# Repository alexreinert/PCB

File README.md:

Dieses Werk ist lizenziert unter einer [Creative Commons Namensnennung - Nicht-kommerziell - Weitergabe unter gleichen Bedingungen 4.0 International Lizenz](http://creativecommons.org/licenses/by-nc-sa/4.0/).

Bei Nutzung der Platinen freue ich mich über Feedback und kleine Aufmerksamkeiten aus meiner [Amazon Wunschliste](https://www.amazon.de/gp/registry/wishlist/3NNUQIQO20AAP/ref=nav_wishlist_lists_1).

Viele Platinen gibt es auch im offiziellen Shop [viopcb](https://www.viopcb.de/).

# PCB
## HB-RF-ETH
Eine Platine um die Homematic Funkmodule HM-MOD-RPI-PCB und RPI-RF-MOD per Netzwerk anschließen zu können.

[Schaltplan](HB-RF-ETH/HB-RF-ETH.pdf)
Die Platine benötigt spezielle Treiber, welche in [debmatic](https://github.com/alexreinert/debmatic) und in [piVCCU3](https://github.com/alexreinert/piVCCU) verfügbar sind.
Eine passende Firmware findet sich unter [HB-RF-ETH](https://github.com/alexreinert/HB-RF-ETH).
Diese Platine ist auch als fertig bestückter Bausatz erhältlich bei [viopcb](https://www.viopcb.de/produkt/bausatz-hb-rf-eth-mit-poe/).

### Benötigte Bauteile:
Siehe Schaltplan

## HB-RF-USB-2
Eine Platine um die Homematic Funkmodule HM-MOD-RPI-PCB und RPI-RF-MOD per USB anschließen zu können.

[Schaltplan](HB-RF-USB-2/HB-RF-USB-2.pdf)
Die Platine benötigt spezielle Treiber, diese sind in [debmatic](https://github.com/alexreinert/debmatic) ab Version 3.51.6-45 und in [piVCCU3](https://github.com/alexreinert/piVCCU) ab Version 3.51.6-40 eingebaut.
Diese Platine ist auch als fertig bestückter Bausatz erhältlich bei [viopcb](https://www.viopcb.de/produkt/bausatz-hb-rf-usb-2/).

### Benötigte Bauteile:
* 1x CP2102N (U1)
* 1x SRV05-4 (U2)
* 2x Kerko 10nF 0402 (C1, C2)
* 6x Kerko 100nF 0402 (C3, C5, C7, C8, C9, C10)
* 2x Kerko 4.7uF 0603 (C4, C6)
* 1x Ferrite Bead 100Ohm, 800mA 0805 (L1)
* 2x AO3401A (Q1, Q2)
* 1x AO3400A (Q3)
* 1x S8050 (Q4)
* 1x Widerstand 1M 0402 (R1)
* 3x Widerstand 1K 0402 (R2, R6, R7)
* 4x Widerstand 10K 0402 (R3, R4, R5, R8)
* 1x USB B Buchse B1HSW6 (J1)
* 1x Pinheader 2x20 (J2)

### EEPROM flashen
[Anleitung](https://hb-programmer.areinert.de)

## HB-RF-USB
Eine Platine um die Homematic Funkmodule HM-MOD-RPI-PCB und RPI-RF-MOD per USB anschließen zu können.

[Schaltplan](HB-RF-USB/HB-RF-USB.pdf)
Die Platine benötigt spezielle Treiber, diese sind in [piVCCU3](https://github.com/alexreinert/piVCCU) ab Version 3.41.11-13, in [debmatic](https://github.com/alexreinert/debmatic) und in [RaspberryMatic](https://github.com/jens-maus/RaspberryMatic) ab Version 3.41.11.20190126 eingebaut.
Diese Platine ist auch erhältlich bei [viopcb](https://www.viopcb.de/produkt/platine-hb-rf-usb/)

### Benötigte Bauteile:
* 1x FTDI FT232RL (U1)
* 1x Micro USB Connector U-F-M5DD-Y-1 (bis Rev. 1.3 MK5P Micro USB Connector)
* 1x Kerko 4.7nF 0805 (C9)
* 1x Kerko 10nF 0805 (C7)
* 6x Kerko 100nF 0805 (C1-C6)
* 1x Kerko 4.7uF 0805 (C8)
* 2x Widerstand 1K 0805 (R2, R3)
* 2x Widerstand 10K 0805 (R1, R5)
* 1x Widerstand 1M 0805 (R4)
* 1x Ferritperle 30 Ohm 0805 (L1)
* 2x IRLML6402 (Q1, Q2)
* 1x IRLML2502 (Q3)
* 1x Pinheader 2*6
* 1x Pinheader 2*20

### EEPROM flashen
[Anleitung](https://hb-programmer.areinert.de)

## HB-UNI-SEN-BATT
Eine universelle Platine für Homebrew Geräte basierend auf [AskSin++ Library](https://github.com/pa-pa/AskSinPP)

[Schaltplan](HB-UNI-SEN-BATT/HB-UNI-SEN-BATT.pdf)
Diese Platine ist auch erhältlich bei [viopcb](https://www.viopcb.de/produkt/platine-hb-uni-sen-batt/).

### Benötigte Bauteile:
* Arduino Pro Mini 3.3V 8Mhz (The Simple)
* CC1101 Modulplatine 868MHz
* 2x LEDs 3mm Low Current (Pin 4 und 5)
* 2x 470Ohm Widerstände (Vorwiderstand für LEDs)
* Elko 10uF 1,5mm
* 2x Goobay Batteriehalter Mignon Print
* Mikroschalter 6*6mm
* Stiftleiste RM 2mm 1x8 Pin (Für CC1101)
* Stiftleiste RM 2,54MM (nach Bedarf)
* IRLU024N (optional für Verpolungsschutz)
* 100KOhm Widerstand (optional für Verpolungsschutz)
* 2x 10KOhm Widerstand (optional Pullup für I2C)

### Passendes Gehäuse
* Camdenboss CBRS01SWH und CBRS01VWH

### Hinweise
* Achtung: Kein Überspannungschutz vorhanden
* Der Verpolungsschutz ist optional. Dafür Bauteil Q1 (IRLU024N) und R3 (100KOhm Widerstand) bestücken. Alternativ J8 auf der Platinenrückseite brücken um ohne Verpolungsschutz zu arbeiten.

## HB-UNI-SEN-PCB
Eine universelle Platine für Homebrew Geräte basierend auf [AskSin++ Library](https://github.com/pa-pa/AskSinPP)

[Schaltplan](HB-UNI-SEN-PCB/HB-UNI-SEN-PCB.pdf)
Diese Platine ist auch erhältlich bei [viopcb](https://www.viopcb.de/produkt/platine-hb-uni-sen-pcb/).

### Benötigte Bauteile:
* Arduino Pro Mini 3.3V 8Mhz (The Simple)
* CC1101 Modulplatine 868MHz
* 1x LEDs 3mm Low Current (Pin 4)
* 1x 470Ohm Widerstände (Vorwiderstand für LEDs)
* Mikroschalter 6*6mm
* Stiftleiste RM 2mm 1x8 Pin (Für CC1101)
* Stiftleiste RM 2,54MM (nach Bedarf)
* Optional: 2x 10KOhm Widerstand und 2x 10KOhm PTC (Temperaturmessung mit PTC an A0 und A1)

### Hinweise
* Achtung: kein Verpolungs- oder Überspannungschutz vorhanden
* Am I2C sind keine Pullups vorhanden, da diese im Regelfall auf I2C Platinen bereits integriert sind
* Aktuell fehlt noch ein Kondensator am VCC vom CC1101.

## HB-UNI-644 (Rev. 2)
Eine universelle Platine für Homebrew Geräte basierend auf [AskSin++ Library](https://github.com/pa-pa/AskSinPP) und dem ATmega644PA

[Schaltplan](HB-UNI-644/HB-UNI-644.pdf)
Diese Platine ist auch erhältlich bei [viopcb](https://www.viopcb.de/produkt/platine-hb-uni-644-rev-2/).

### Benötigte Bauteile:
#### Grundfunktion
* ATmega644PA oder ATmega1284P (TQFP44) (U1)
* CC1101 Modulplatine 868MHz ggf. mit RM 2.0 Pinheader (U2)
* 1x Kerko 10uF 0805 (C13)
* 7x Kerko 100nF 0805 (C1-C6, C14)
* 2x Widerstand 330 Ohm 0805 (R2, R3)
* 1x Widerstand 10K Ohm 0805 (R1)
* 1x Triple Color LED Common Cathode THT (D1)
* 1x Tactile Switch 2 Pin 6x3.5 SMD (SW1)
* 1x Quarz 8 Mhz HC49 THT (Y1) (optional)
* 2x Kerko 22pF 0805 (C7, C8) (optional für Quarz)
* Pinheader nach Bedarf

#### Power Option 1: Batteriebetrieb mit Step-Up
* 2x Goobay Batteriehalter Mignon Print
* 1x Widerstand 470K Ohm 0805 (R5)
* 1x Widerstand 100K Ohm 0805 (R6)
* 1x MAX1724EZK33 (U3)
* 1x LQH43CN100K03L (L1)
* 1x Kerko 10uF 0805 (C9)
* 1x Kerko 33uF 1206 (C10)
##### Verpolungsschutz und Überlastschutz
* 1x IRLML6244 (Q1)
* 1x Widerstand 100K Ohm 0805 (R4)
* 1x PTC 6V/250mA 1206 (F1)

#### Power Option 2: Externe Stromversorgung mit 5-9V, 100mA
* 1x HT-7533-1 (U4)
* 1x Kerko 10uF 50V 1206 (C11)
* 1x Kerko 10uF 0805 (C12)
* 1x Elko 1000uF 8mm*12mm (C15)
##### Verpolungsschutz und Überlastschutz
* 1x IRLML5203 (Q2)
* 1x Widerstand 100K Ohm 0805 (R11)
* 1x PTC 16V/250mA 1206 (F1)

#### Power Option 3: Externe Stromversorgung 5-24V, 1A
* 1x [MP2315 Power Module](https://de.aliexpress.com/item/DC-DC-R-cktritt-Abw-rtswandler-Einstellbar-4-5-V-24-V-zu-5-V-3A/32833398745.html)
   Kontakt zum Trimmer durchtrennen, Lötbrücke bei 3.3V anbringen
* 1x Elko 1000uF 8mm*12mm (C15)
##### Verpolungsschutz und Überlastschutz
* 1x IRF4905S (Q3)
* 1x Widerstand 100K Ohm 0805 (R12)
* 1x Zener 16V MiniMelf (D2)
* 1x PTC 30V/2A 1206 (F1)

#### I2C Pullup Widerstände (optional)
* 2x Widerstand 10k Ohm 0805 (R7, R8)

#### Vorwiderstände für NTC Messung an A0 und A1
* 2x Widerstand 10k Ohm 0805 (R9, R10)

### Passendes Gehäuse
* Camdenboss CBRS01SWH und CBRS01VWH

### Betrieb mit 5V, 16MHz bei Netzbetrieb
* Der MC kann auch mit 5V und dann mit 16MHz betrieben werden, dafür müssen ggü. oben folgende Anpassungen gemacht werden:
* Nicht möglich bei Power Option 1
* Bei Power Option 2: HT-7550-1 statt HT-7533-1 uf U4, Eingangsspannung >= 6V
* Bei Power Option 3: Lötbrücke auf MP2315 Modul bei 5V statt bei 3.3V, Eingangsspannung >= 6V
* CC1101 auf Position U5 statt auf U2
* Nicht bestücken: C13, C14
* Quarz Y1 mit 16MHz statt 8MHz
* Zusätzliche Bauteile
   * 1x LM-3480-3.3 (U6)
   * 1x TXS0108EPWR (U7)
   * 3x Kerko 10uF 0805 (C16, C18, C19)
   * 3x Kerko 100nF 0805 (C17, C20, C21)
* ACHTUNG: Alle VCC Pins laufen dann auf 5V, auch z.B. die vom I2C

### Hinweise
* Auch wenn die meisten Bauteile SMD sind, so ist die Platine für Handlötung entwickelt. Dementsprechend sind alle Teile mind. 0805 mit vergrößerten Pads für Handlötung.
* Es darf immer nur eine Power Option genutzt und bestückt werden
* Die rechte Seite der Platine kann entfernt werden, wenn die Batteriehalter oder das MP2315 Power Module nicht benötigt werden, es laufen keine Leiterbahnen rechts der Fräsung (abgesehen von denen für die Batterie bzw. Power Module)
* Die Lötbrücke J2 muss immer geschlossen werden, außer es wird der Verpolungsschutz für Batteriebetrieb verwendet
* Falls eine externe Spannung von 3.3V ohne Spannungsanpassung, Verpolungsschutz und Überlastschutz verwendet werden soll, dann muss die Lötbrücke J4 geschlossen werden
* Die Anschlüsse an J9 sind zusammen mit J12 genau passend für die Platine CJMCU-2803 um an den Anschlüssen ein Darlington Array zu verwenden (Jeder der Ports ist dann mit 500mA belastbar)
* Beschriftung der Anschlüsse folgt dem Bobuino Pinout

## HB-UNI-SEN-WEA
Eine passende Platine für den [Wettersensor von Jérôme](https://github.com/jp112sdl/HB-UNI-Sen-WEA/)

[Schaltplan](HB-UNI-SEN-WEA/HB-UNI-SEN-WEA.pdf)
Diese Platine ist auch erhältlich bei [viopcb](https://www.viopcb.de/produkt/platine-hb-uni-sen-wea/).

### Benötigte Bauteile:
* Arduino Pro Mini 3.3V 8Mhz (The Simple)
* CC1101 Modulplatine 868MHz
* Elko 10uF 1,5mm
* Mikroschalter 6*6mm
* Kerko 1nf RM 2.5mm
* 10K Widerstand
* 100K Widerstand
* MPSA13 TO-92
* 4x Molex Spox 2-pol (Alternativ Stiftleiste oder Kabel direkt anlöten)
* 4x Molex Spox 4-pol (Alternativ Stiftleiste oder Kabel direkt anlöten)
* 1x Molex Spox 7-pol (Alternativ Stiftleiste oder Kabel direkt anlöten)
* Stiftleiste RM 2mm 1x8 Pin (Für CC1101)

### Hinweise
* Achtung: kein Verpolungs- oder Überspannungschutz vorhanden
* Am I2C sind keine Pullups vorhanden, da diese im Regelfall auf I2C Platinen bereits integriert sind

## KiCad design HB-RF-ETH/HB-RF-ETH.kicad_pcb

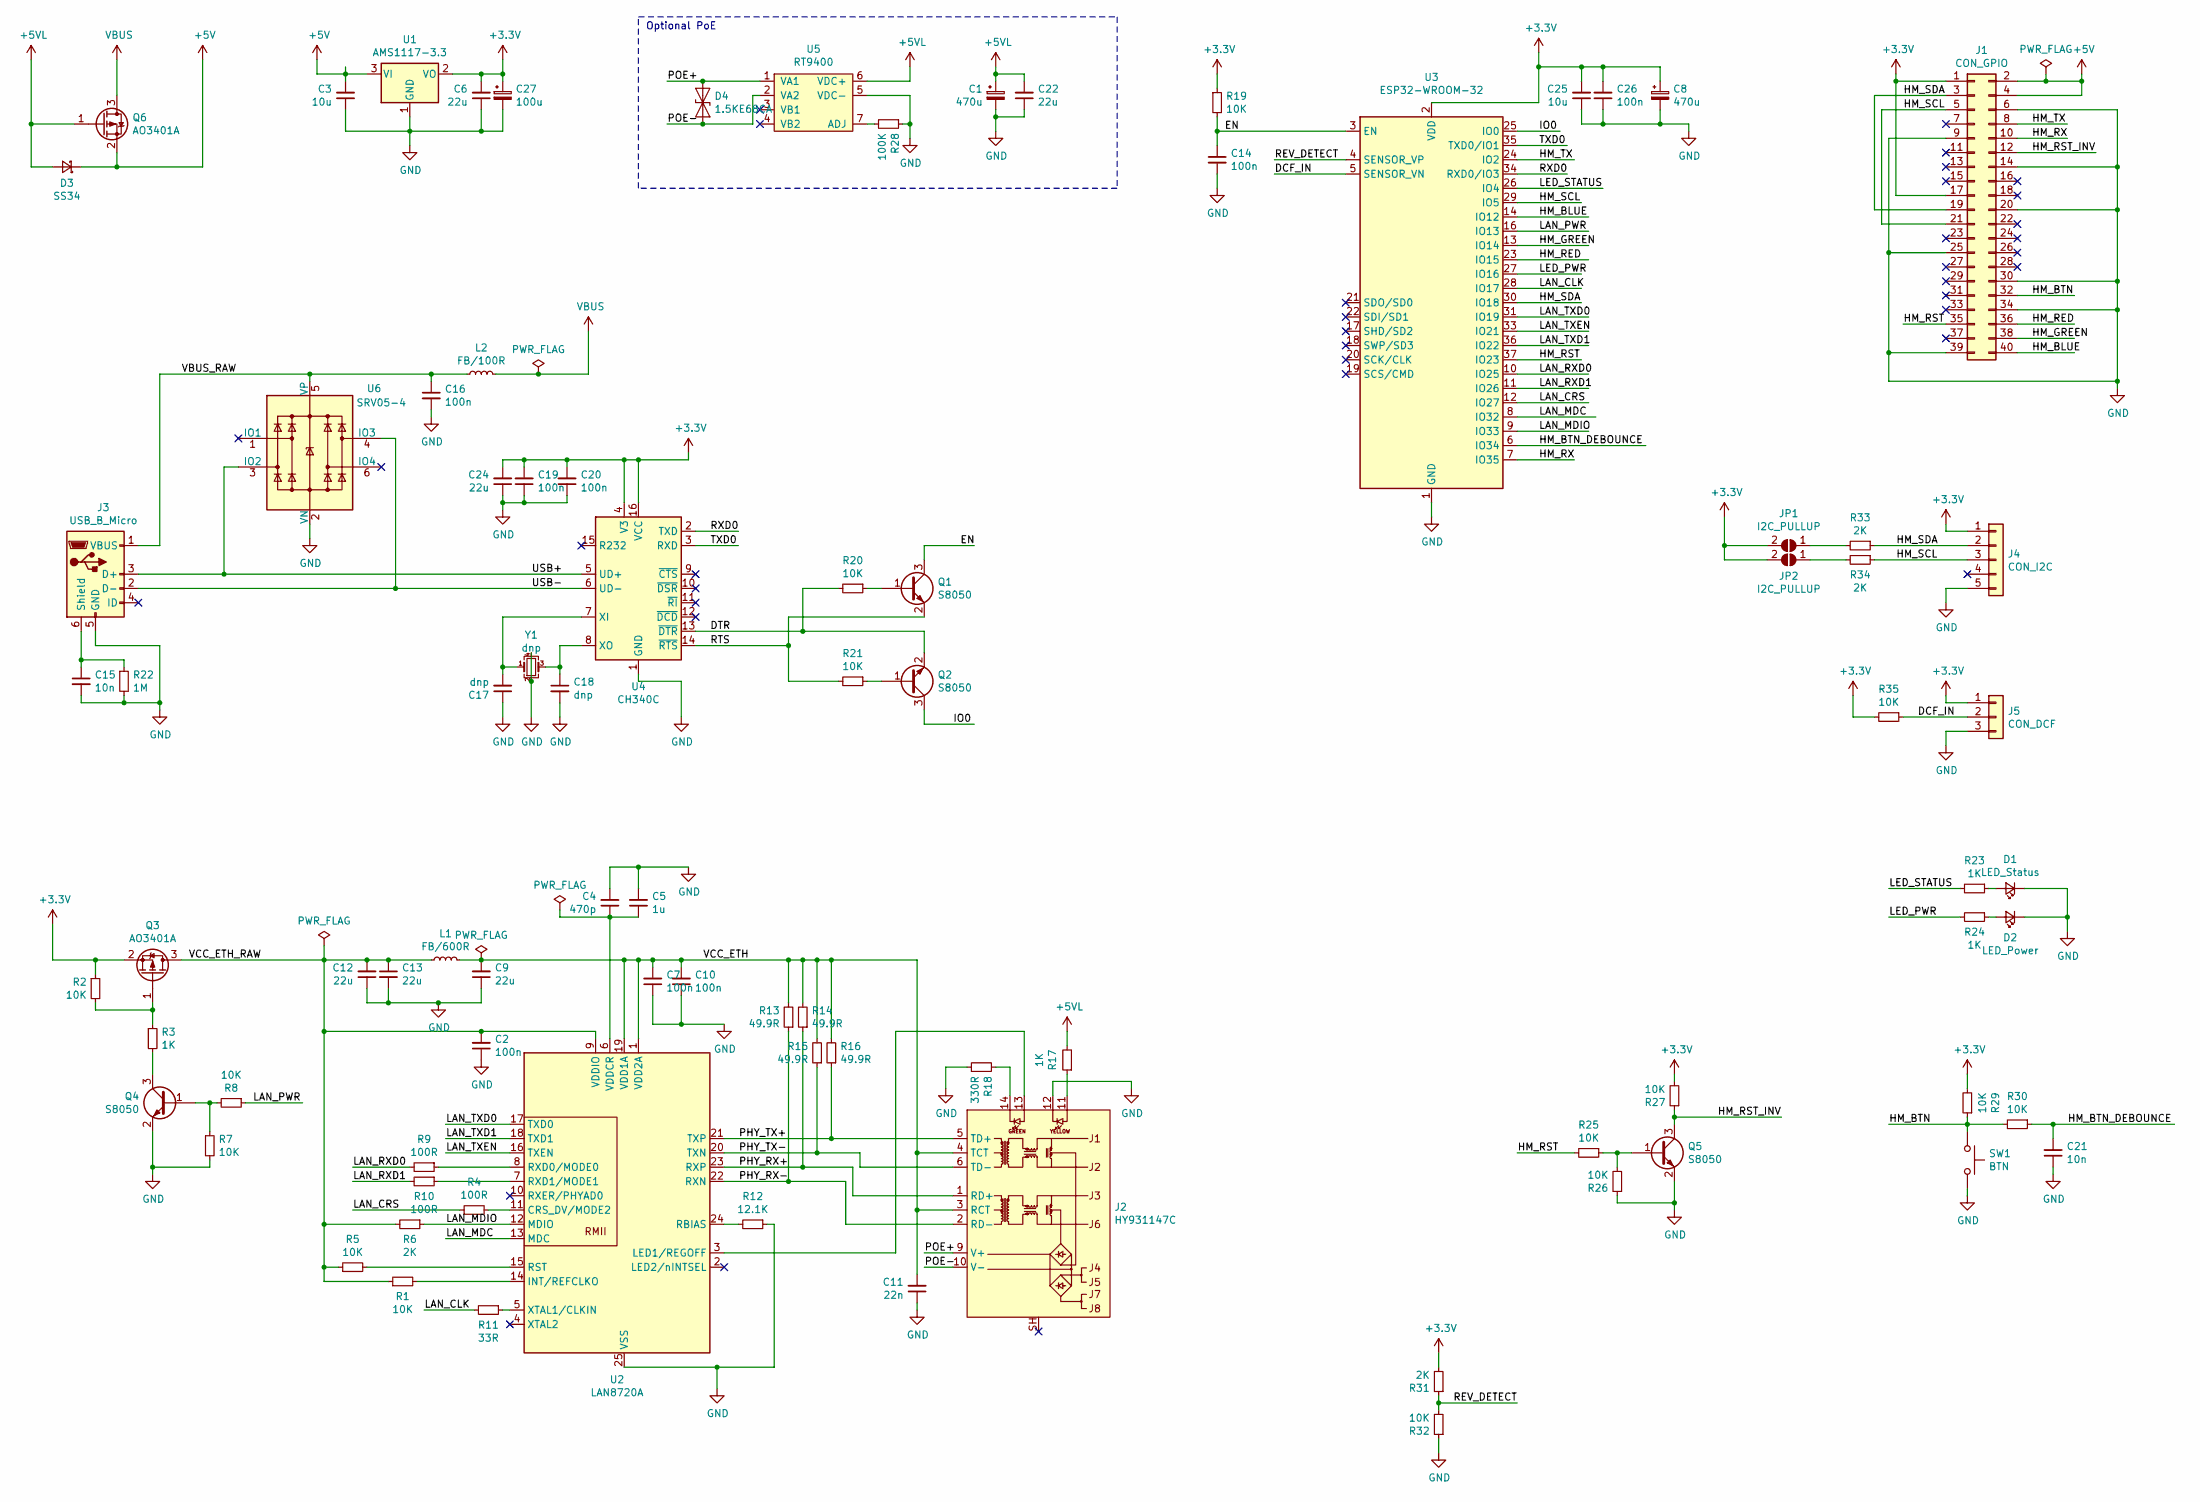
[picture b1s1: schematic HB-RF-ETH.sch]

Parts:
C1, C8: 470u; CP_Radial_D8.0mm_P3.50mm
C2, C7, C10, C14, C16, C19, C20, C26: 100n; C_0402_1005Metric; LCSC C1525
C3, C25: 10u; C_0603_1608Metric; LCSC C19702
C4: 470p; C_0402_1005Metric; LCSC C1537
C5: 1u; C_0603_1608Metric; LCSC C15849
C6, C9, C12, C13, C22, C24: 22u; C_0603_1608Metric; LCSC C59461
C11: 22n; C_0402_1005Metric; LCSC C1532
C15, C21: 10n; C_0402_1005Metric; LCSC C15195
C17, C18: dnp; C_0402_1005Metric
C27: 100u; CP_EIA-3528-15_AVX-H; LCSC C16133
D1: LED_Status; LED_0603_1608Metric_Castellated; LCSC C2286
D2: LED_Power; LED_0603_1608Metric_Castellated; LCSC C72043
D3: SS34; D_SMA; LCSC C8678
D4: 1.5KE68CA; D_DO-201AE_P5.08mm_Vertical_KathodeUp
J1: CON_GPIO; PinHeader_2x20_P2.54mm_Vertical
J2: HY931147C; RJ45_Hanrun_HY934711C
J3: USB_B_Micro; U-F-M5DD-Y-1
J4: CON_I2C; PinHeader_1x05_P2.54mm_Vertical
J5: CON_DCF; PinHeader_1x03_P2.54mm_Vertical
JP1, JP2: I2C_PULLUP; SolderJumper-2_P1.3mm_Open_RoundedPad1.0x1.5mm
L1: FB/600R; L_0805_2012Metric; LCSC C1017
L2: FB/100R; L_0805_2012Metric; LCSC C1015
Q1, Q2, Q4, Q5: S8050; SOT-23; LCSC C2146
Q3, Q6: AO3401A; SOT-23; LCSC C15127
R1, R2, R5, R7, R8, R19, R20, R21, R25, R26, R27, R29, R30, R32, R35: 10K; R_0402_1005Metric; LCSC C25744
R3, R17, R23, R24: 1K; R_0402_1005Metric; LCSC C11702
R4, R9, R10: 100R; R_0402_1005Metric; LCSC C25076
R6, R31, R33, R34: 2K; R_0402_1005Metric; LCSC C4109
R11: 33R; R_0402_1005Metric; LCSC C25105
R12: 12.1K; R_0402_1005Metric; LCSC C25852
R13, R14, R15, R16: 49.9R; R_0402_1005Metric; LCSC C25120
R18: 330R; R_0402_1005Metric; LCSC C25104
R22: 1M; R_0402_1005Metric; LCSC C26083
R28: 100K; R_0402_1005Metric; LCSC C25741
SW1: BTN; SW_PUSH_6mm
U1: AMS1117-3.3; SOT-223-3_TabPin2; LCSC C6186
U2: LAN8720A; QFN-24-1EP_4x4mm_P0.5mm_EP2.6x2.6mm_ThermalVias; LCSC C45223
U3: ESP32-WROOM-32; ESP32-WROOM-32_Handsoldering
U4: CH340C; SOIC-16_3.9x9.9mm_P1.27mm; LCSC C84681
U5: RT9400
U6: SRV05-4; SOT-23-6; LCSC C85364
Y1: dnp; Crystal_SMD_3225-4Pin_3.2x2.5mm

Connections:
+3V3: C6.2, C8.1, C19.2, C20.2, C24.2, C25.2, C26.2, C27.1, J1.1, J1.17, J4.1, J5.1, JP1.2 (B), JP2.2 (B), Q3.2 (S), R2.1, R19.1, R27.2, R29.2, R31.2, R35.2, U1.2 (VO), U3.2 (VDD), U4.4 (V3), U4.16 (VCC)
+5V: C3.2, D3.1 (K), J1.2, J1.4, Q6.2 (S), U1.3 (VI)
+5VL: C1.1, C22.2, D3.2 (A), Q6.1 (G), R17.2, U5.6 (VDC+)
/DCF_IN: J5.2, R35.1, U3.5 (SENSOR_VN)
/DTR: Q2.2 (E), R20.2, U4.13 (~DTR)
/EN: C14.1, Q1.3 (C), R19.2, U3.3 (EN)
/HM_BLUE: J1.40, U3.14 (IO12)
/HM_BTN: J1.32, R29.1, R30.2, SW1.1
/HM_BTN_DEBOUNCE: C21.2, R30.1, U3.6 (IO34)
/HM_GREEN: J1.38, U3.13 (IO14)
/HM_RED: J1.36, U3.23 (IO15)
/HM_RST: J1.35, R25.2, U3.37 (IO23)
/HM_RST_INV: J1.12, Q5.3 (C), R27.1
/HM_RX: J1.10, U3.7 (IO35)
/HM_SCL: J1.5, J1.21, J4.3, R34.1, U3.29 (IO5)
/HM_SDA: J1.3, J1.19, J4.2, R33.1, U3.30 (IO18)
/HM_TX: J1.8, U3.24 (IO2)
/IO0: Q2.3 (C), U3.25 (IO0)
/LAN_CLK: R11.2, U3.28 (IO17)
/LAN_CRS: R4.1, U3.12 (IO27)
/LAN_MDC: U2.13 (MDC), U3.8 (IO32)
/LAN_MDIO: R6.1, U2.12 (MDIO), U3.9 (IO33)
/LAN_PWR: R8.1, U3.16 (IO13)
/LAN_RXD0: R9.2, U3.10 (IO25)
/LAN_RXD1: R10.2, U3.11 (IO26)
/LAN_TXD0: U2.17 (TXD0), U3.31 (IO19)
/LAN_TXD1: U2.18 (TXD1), U3.36 (IO22)
/LAN_TXEN: U2.16 (TXEN), U3.33 (IO21)
/LED_PWR: R24.2, U3.27 (IO16)
/LED_STATUS: R23.2, U3.26 (IO4)
/PHY_RX+: J2.1 (RD+), R14.1, U2.23 (RXP)
/PHY_RX-: J2.2 (RD-), R13.1, U2.22 (RXN)
/PHY_TX+: J2.5 (TD+), R16.1, U2.21 (TXP)
/PHY_TX-: J2.6 (TD-), R15.1, U2.20 (TXN)
/POE+: D4.1 (A1), J2.9 (V+), U5.1 (VA1)
/POE-: D4.2 (A2), J2.10 (V-), U5.2 (VA2)
/REV_DETECT: R31.1, R32.2, U3.4 (SENSOR_VP)
/RTS: Q1.2 (E), R21.2, U4.14 (~RTS)
/RXD0: U3.34 (RXD0/IO3), U4.2 (TXD)
/TXD0: U3.35 (TXD0/IO1), U4.3 (RXD)
/USB+: J3.3 (D+), U4.5 (UD+), U6.3 (IO2)
/USB-: J3.2 (D-), U4.6 (UD-), U6.4 (IO3)
/VBUS_RAW: C16.1, J3.1 (VBUS), L2.1, U6.5 (VP)
/VCC_ETH: C7.2, C9.2, C10.2, C11.2, J2.3 (RCT), J2.4 (TCT), L1.2, R13.2, R14.2, R15.2, R16.2, U2.1 (VDD2A), U2.19 (VDD1A)
/VCC_ETH_RAW: C2.2, C12.2, C13.1, L1.1, Q3.3 (D), R1.1, R5.1, R6.2, U2.9 (VDDIO)
GND: C1.2, C2.1, C3.1, C4.2, C5.2, C6.1, C7.1, C8.2, C9.1, C10.1, C11.1, C12.1, C13.2, C14.2, C15.2, C16.2, C17.1, C18.2, C19.1, C20.1, C21.1, C22.1, C24.1, C25.1, C26.1, C27.2, D1.1 (K), D2.1 (K), J1.6, J1.9, J1.14, J1.20, J1.25, J1.30, J1.34, J1.39, J2.12, J3.5 (GND), J4.5, J5.3, Q4.2 (E), Q5.2 (E), R7.2, R12.1, R18.1, R22.2, R26.1, R28.1, R32.1, SW1.2, U1.1 (GND), U2.25 (VSS), U3.1 (GND), U3.15 (GND), U3.38 (GND), U3.39 (GND), U4.1 (GND), U5.5 (VDC-), U6.2 (VN), Y1.2, Y1.4
unnamed: C4.1, C5.1, U2.6 (VDDCR)
unnamed: C15.1, J3.6 (Shield), R22.1
unnamed: C17.2, U4.7 (XI), Y1.1
unnamed: C18.1, U4.8 (XO), Y1.3
unnamed: D1.2 (A), R23.1
unnamed: D2.2 (A), R24.1
unnamed: J2.11, R17.1
unnamed: J2.13, U2.3 (LED1/REGOFF)
unnamed: J2.14, R18.2
unnamed: JP1.1 (A), R33.2
unnamed: JP2.1 (A), R34.2
unnamed: Q1.1 (B), R20.1
unnamed: Q2.1 (B), R21.1
unnamed: Q3.1 (G), R2.2, R3.1
unnamed: Q4.1 (B), R7.1, R8.2
unnamed: Q4.3 (C), R3.2
unnamed: Q5.1 (B), R25.1, R26.2
unnamed: R1.2, U2.14 (INT/REFCLKO)
unnamed: R4.2, U2.11 (CRS_DV/MODE2)
unnamed: R5.2, U2.15 (RST)
unnamed: R9.1, U2.8 (RXD0/MODE0)
unnamed: R10.1, U2.7 (RXD1/MODE1)
unnamed: R11.1, U2.5 (XTAL1/CLKIN)
unnamed: R12.2, U2.24 (RBIAS)
unnamed: R28.2, U5.7 (ADJ)
VBUS: L2.2, Q6.3 (D)

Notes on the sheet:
Optional PoE

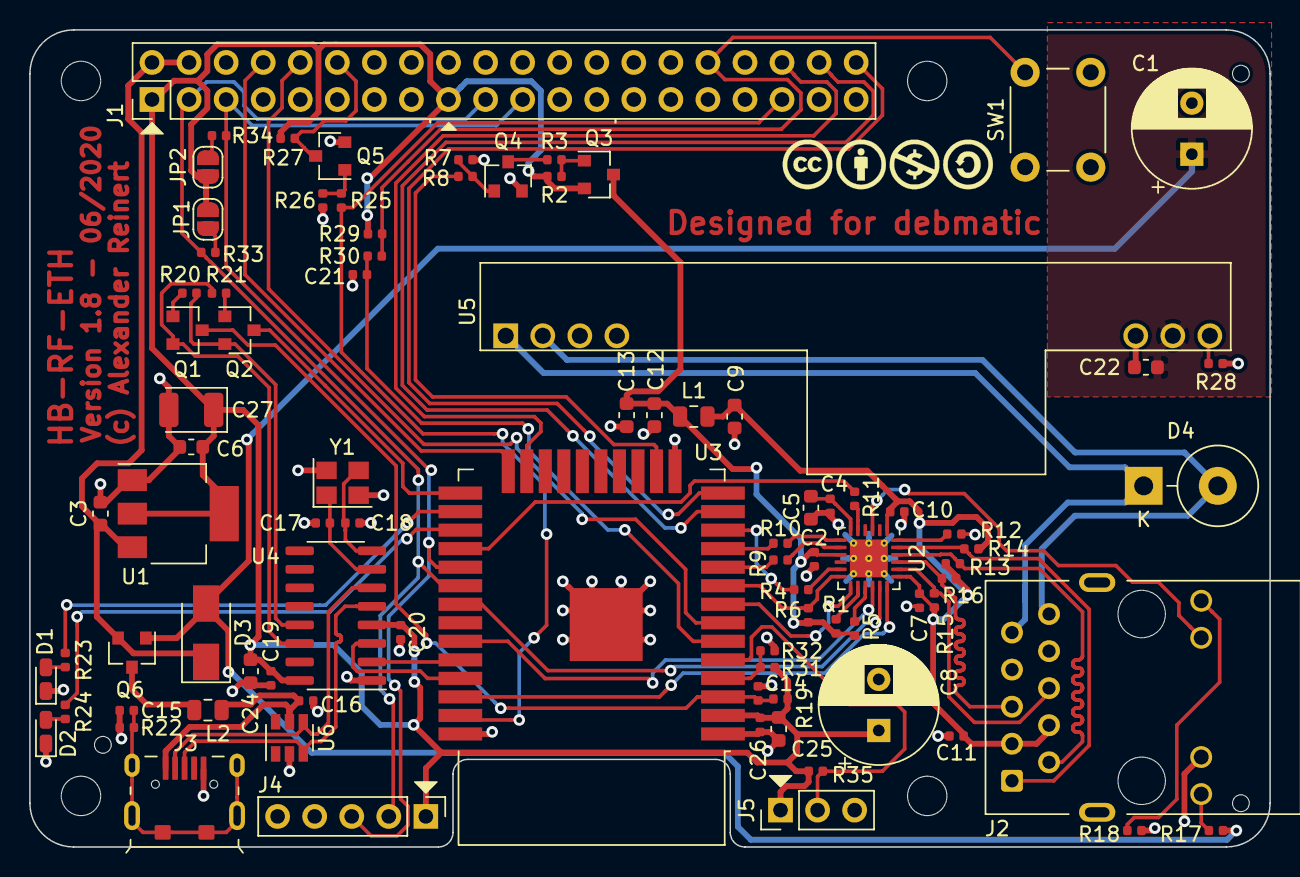
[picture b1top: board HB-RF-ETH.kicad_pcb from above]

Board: 2 copper layers, 85.0 x 56.0 mm, 88 parts (0 on the bottom side), 72 nets.

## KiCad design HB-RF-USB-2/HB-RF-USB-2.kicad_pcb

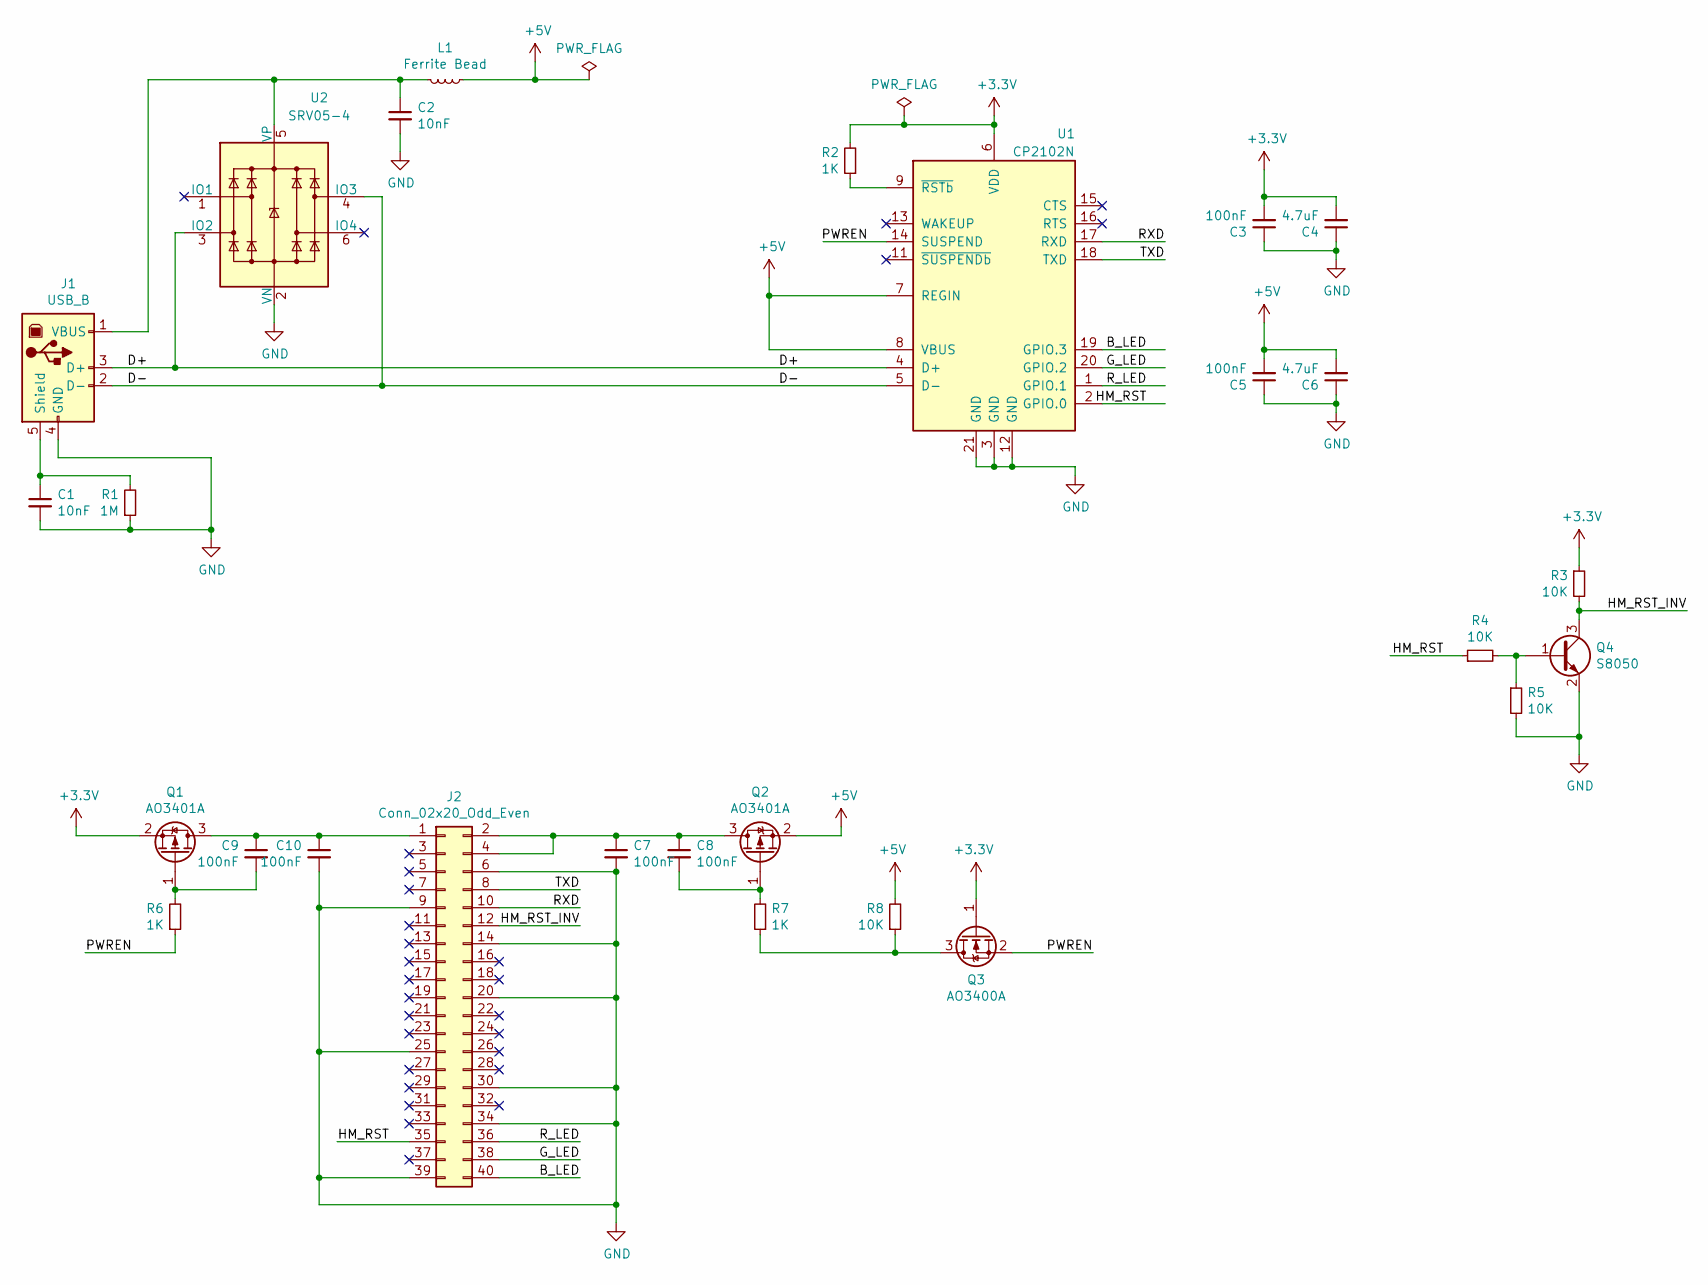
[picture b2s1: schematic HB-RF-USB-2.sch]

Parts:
C1, C2: 10nF; C_0402_1005Metric; LCSC C15195
C3, C5, C7, C8, C9, C10: 100nF; C_0402_1005Metric; LCSC C1525
C4, C6: 4.7uF; C_0603_1608Metric; LCSC C19666
J1: USB_B; USB_B_OST_USB-B1HSxx_Horizontal
J2: Conn_02x20_Odd_Even; PinHeader_2x20_P2.54mm_Vertical
L1: Ferrite Bead; L_0805_2012Metric; LCSC C1015
Q1, Q2: AO3401A; SOT-23; LCSC C15127
Q3: AO3400A; SOT-23; LCSC C20917
Q4: S8050; SOT-23; LCSC C2146
R1: 1M; R_0402_1005Metric; LCSC C26083
R2, R6, R7: 1K; R_0402_1005Metric; LCSC C11702
R3, R4, R5, R8: 10K; R_0402_1005Metric; LCSC C25744
U1: CP2102N; SiliconLabs_QFN-20-1EP_3x3mm_P0.5mm; LCSC C89049
U2: SRV05-4; SOT-23-6; LCSC C85364

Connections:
+3V3: C3.2, C4.2, Q1.2 (S), Q3.1 (G), R2.2, R3.1, U1.6 (VDD)
+5V: C5.2, C6.2, L1.1, Q2.2 (S), R8.2, U1.7 (REGIN), U1.8 (VBUS)
/B_LED: J2.40, U1.19 (GPIO.3)
/D+: J1.3 (D+), U1.4 (D+), U2.3 (IO2)
/D-: J1.2 (D-), U1.5 (D-), U2.4 (IO3)
/G_LED: J2.38, U1.20 (GPIO.2)
/HM_RST: J2.35, R4.1, U1.2 (GPIO.0)
/HM_RST_INV: J2.12, Q4.3 (C), R3.2
/PWREN: Q3.2 (S), R6.1, U1.14 (SUSPEND)
/RXD: J2.10, U1.17 (RXD)
/R_LED: J2.36, U1.1 (GPIO.1)
/TXD: J2.8, U1.18 (TXD)
GND: C1.2, C2.2, C3.1, C4.1, C5.1, C6.1, C7.2, C10.2, J1.4 (GND), J2.6, J2.9, J2.14, J2.20, J2.25, J2.30, J2.34, J2.39, Q4.2 (E), R1.1, R5.2, U1.3 (GND), U1.12 (GND), U1.21 (GND), U2.2 (VN)
unnamed: C1.1, J1.5 (Shield), R1.2
unnamed: C2.1, J1.1 (VBUS), L1.2, U2.5 (VP)
unnamed: C7.1, C8.1, J2.2, J2.4, Q2.3 (D)
unnamed: C8.2, Q2.1 (G), R7.2
unnamed: C9.2, Q1.1 (G), R6.2
unnamed: C9.1, C10.1, J2.1, Q1.3 (D)
unnamed: Q3.3 (D), R7.1, R8.1
unnamed: Q4.1 (B), R4.2, R5.1
unnamed: R2.1, U1.9 (~RSTb)

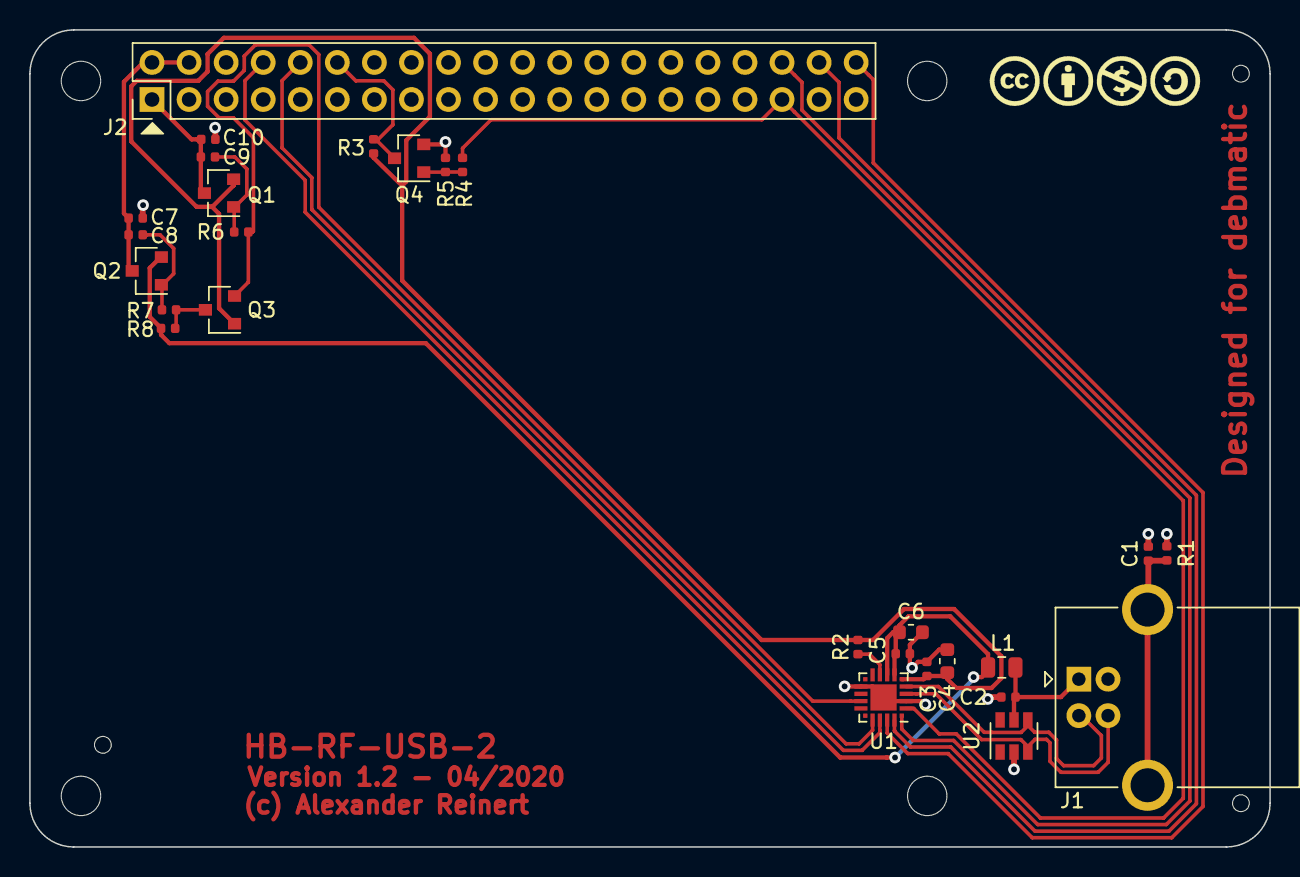
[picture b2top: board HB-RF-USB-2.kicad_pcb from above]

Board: 2 copper layers, 85.0 x 56.0 mm, 27 parts (0 on the bottom side), 22 nets.

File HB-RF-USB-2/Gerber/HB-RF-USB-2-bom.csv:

Comment,Designator,Footprint,LCSC
"10nF","C2,C1","Capacitor_SMD:C_0402_1005Metric","C15195"
"4.7uF","C6,C4","Capacitor_SMD:C_0603_1608Metric","C19666"
"100nF","C8,C7,C9,C10,C5,C3","Capacitor_SMD:C_0402_1005Metric","C1525"
"USB_B","J1","Connector_USB:USB_B_OST_USB-B1HSxx_Horizontal"
"Conn_02x20_Odd_Even","J2","Connector_PinHeader_2.54mm:PinHeader_2x20_P2.54mm_Vertical"
"Ferrite Bead","L1","Inductor_SMD:L_0805_2012Metric","C1015"
"AO3401A","Q2,Q1","Package_TO_SOT_SMD:SOT-23","C15127"
"AO3400A","Q3","Package_TO_SOT_SMD:SOT-23","C20917"
"S8050","Q4","Package_TO_SOT_SMD:SOT-23","C2146"
"1M","R1","Resistor_SMD:R_0402_1005Metric","C26083"
"1K","R7,R6,R2","Resistor_SMD:R_0402_1005Metric","C11702"
"10K","R8,R4,R5,R3","Resistor_SMD:R_0402_1005Metric","C25744"
"CP2102N","U1","Package_DFN_QFN:SiliconLabs_QFN-20-1EP_3x3mm_P0.5mm","C89049"
"SRV05-4","U2","Package_TO_SOT_SMD:SOT-23-6","C85364"

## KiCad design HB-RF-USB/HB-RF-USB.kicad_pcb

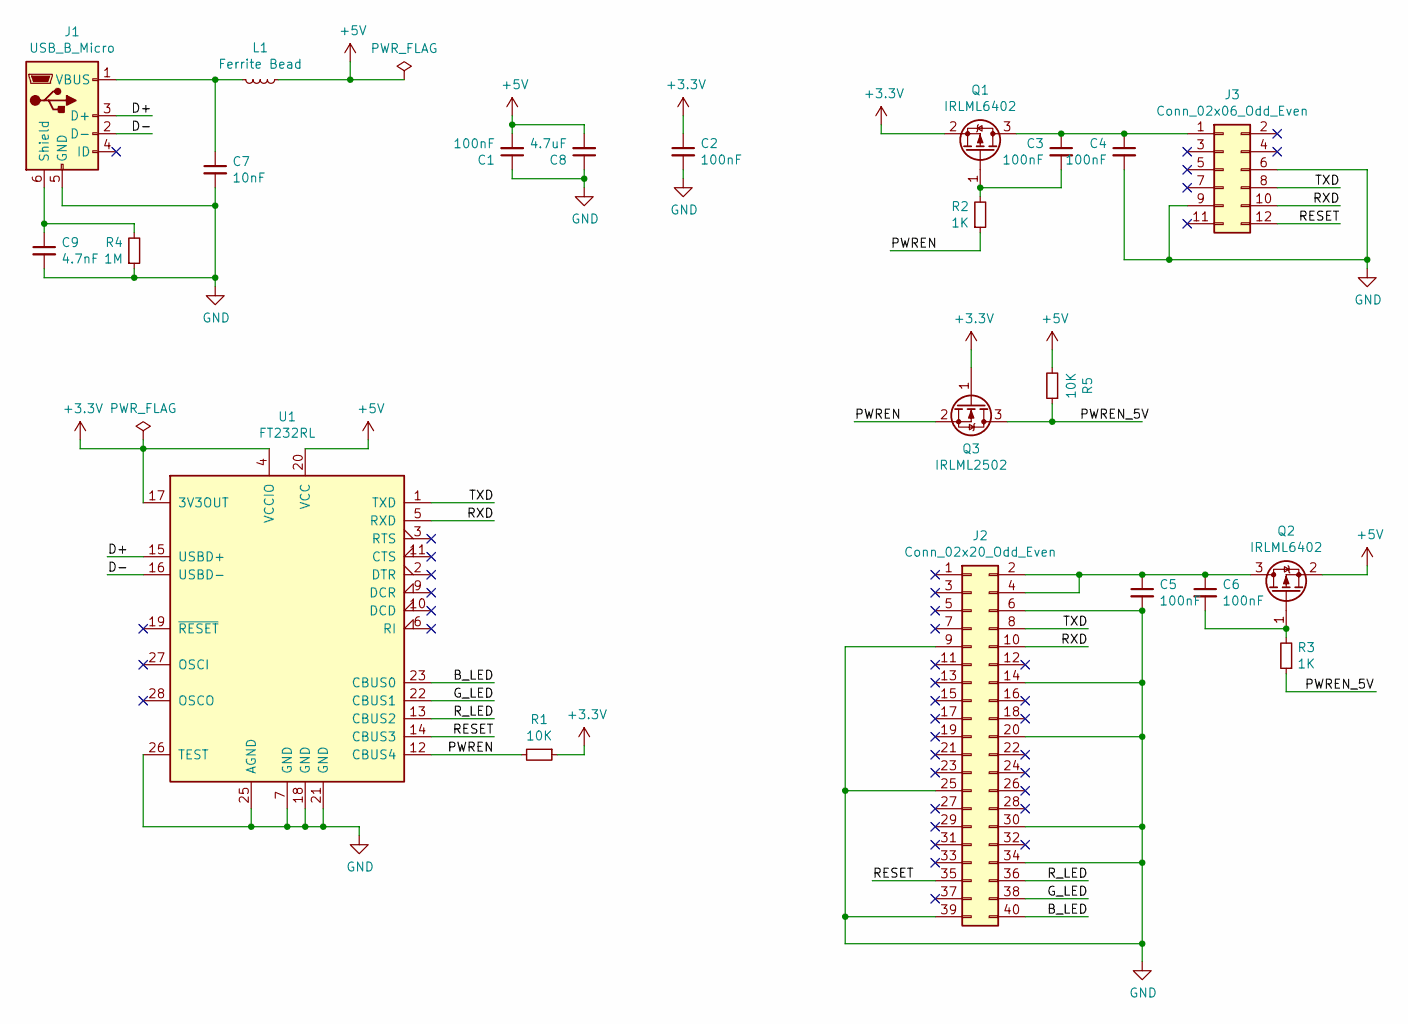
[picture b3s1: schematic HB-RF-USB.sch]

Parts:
C1, C2, C3, C4, C5, C6: 100nF; C_0805_2012Metric_Pad1.15x1.40mm_HandSolder
C7: 10nF; C_0805_2012Metric_Pad1.15x1.40mm_HandSolder
C8: 4.7uF; C_0805_2012Metric_Pad1.15x1.40mm_HandSolder
C9: 4.7nF; C_0805_2012Metric_Pad1.15x1.40mm_HandSolder
J1: USB_B_Micro; U-F-M5DD-Y-1
J2: Conn_02x20_Odd_Even; PinHeader_2x20_P2.54mm_Vertical
J3: Conn_02x06_Odd_Even; PinHeader_2x06_P2.54mm_Vertical
L1: Ferrite Bead; L_0805_2012Metric_Pad1.15x1.40mm_HandSolder
Q1, Q2: IRLML6402; SOT-23_Handsoldering
Q3: IRLML2502; SOT-23_Handsoldering
R1, R5: 10K; R_0805_2012Metric_Pad1.15x1.40mm_HandSolder
R2, R3: 1K; R_0805_2012Metric_Pad1.15x1.40mm_HandSolder
R4: 1M; R_0805_2012Metric_Pad1.15x1.40mm_HandSolder
U1: FT232RL; SSOP-28_5.3x10.2mm_P0.65mm

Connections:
+3V3: C2.1, Q1.2 (S), Q3.1 (G), R1.1, U1.4 (VCCIO), U1.17 (3V3OUT)
+5V: C1.2, C8.2, L1.1, Q2.2 (S), R5.2, U1.20 (VCC)
/B_LED: J2.40, U1.23 (CBUS0)
/D+: J1.3 (D+), U1.15 (USBD+)
/D-: J1.2 (D-), U1.16 (USBD-)
/G_LED: J2.38, U1.22 (CBUS1)
/PWREN: Q3.2 (S), R1.2, R2.1, U1.12 (CBUS4)
/PWREN_5V: Q3.3 (D), R3.1, R5.1
/RESET: J2.35, J3.12, U1.14 (CBUS3)
/RXD: J2.10, J3.10, U1.5 (RXD)
/R_LED: J2.36, U1.13 (CBUS2)
/TXD: J2.8, J3.8, U1.1 (TXD)
GND: C1.1, C2.2, C4.2, C5.2, C7.2, C8.1, C9.2, J1.5 (GND), J2.6, J2.9, J2.14, J2.20, J2.25, J2.30, J2.34, J2.39, J3.6, J3.9, R4.1, U1.7 (GND), U1.18 (GND), U1.21 (GND), U1.25 (AGND), U1.26 (TEST)
unnamed: C3.1, C4.1, J3.1, Q1.3 (D)
unnamed: C3.2, Q1.1 (G), R2.2
unnamed: C5.1, C6.1, J2.2, J2.4, Q2.3 (D)
unnamed: C6.2, Q2.1 (G), R3.2
unnamed: C7.1, J1.1 (VBUS), L1.2
unnamed: C9.1, J1.6 (Shield), R4.2

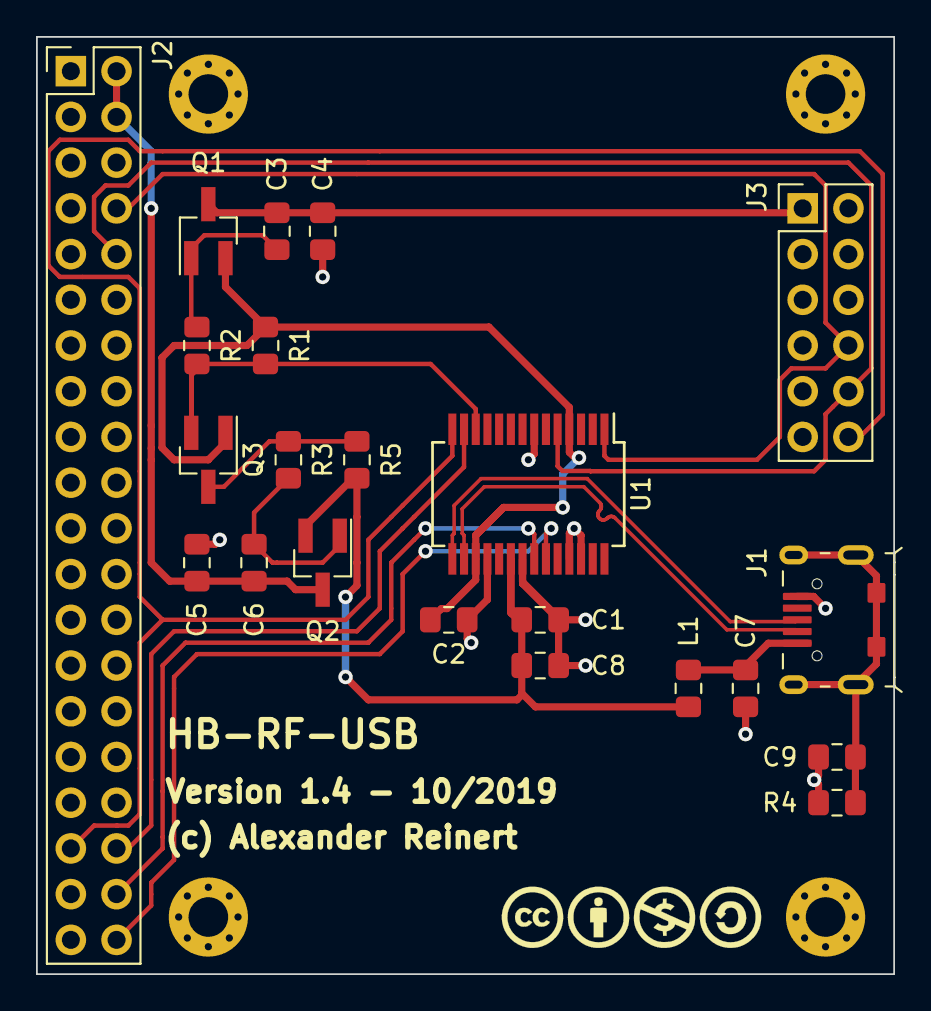
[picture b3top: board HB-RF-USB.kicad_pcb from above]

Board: 2 copper layers, 47.6 x 52.1 mm, 22 parts (0 on the bottom side), 19 nets.

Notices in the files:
README.md:
Creative Commons Lizenzvertrag
